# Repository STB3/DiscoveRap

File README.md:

# DiscoveRap
RpRap Electronics Expansion Board for the STM32F429 Discovery Board<p>
Max. 3 Extruders, X, Y, Z Axis<br>
Heated Bed<br>
Case Fan & Light<br>
Fans for each Extruder<br>
TMC260 Stepper driver<br>
USB-OTG, USB-Virtual COM, SD-Card Storage<br>
WLAN option<br>
Needs the STM32F429 Demoboard for operation<br>

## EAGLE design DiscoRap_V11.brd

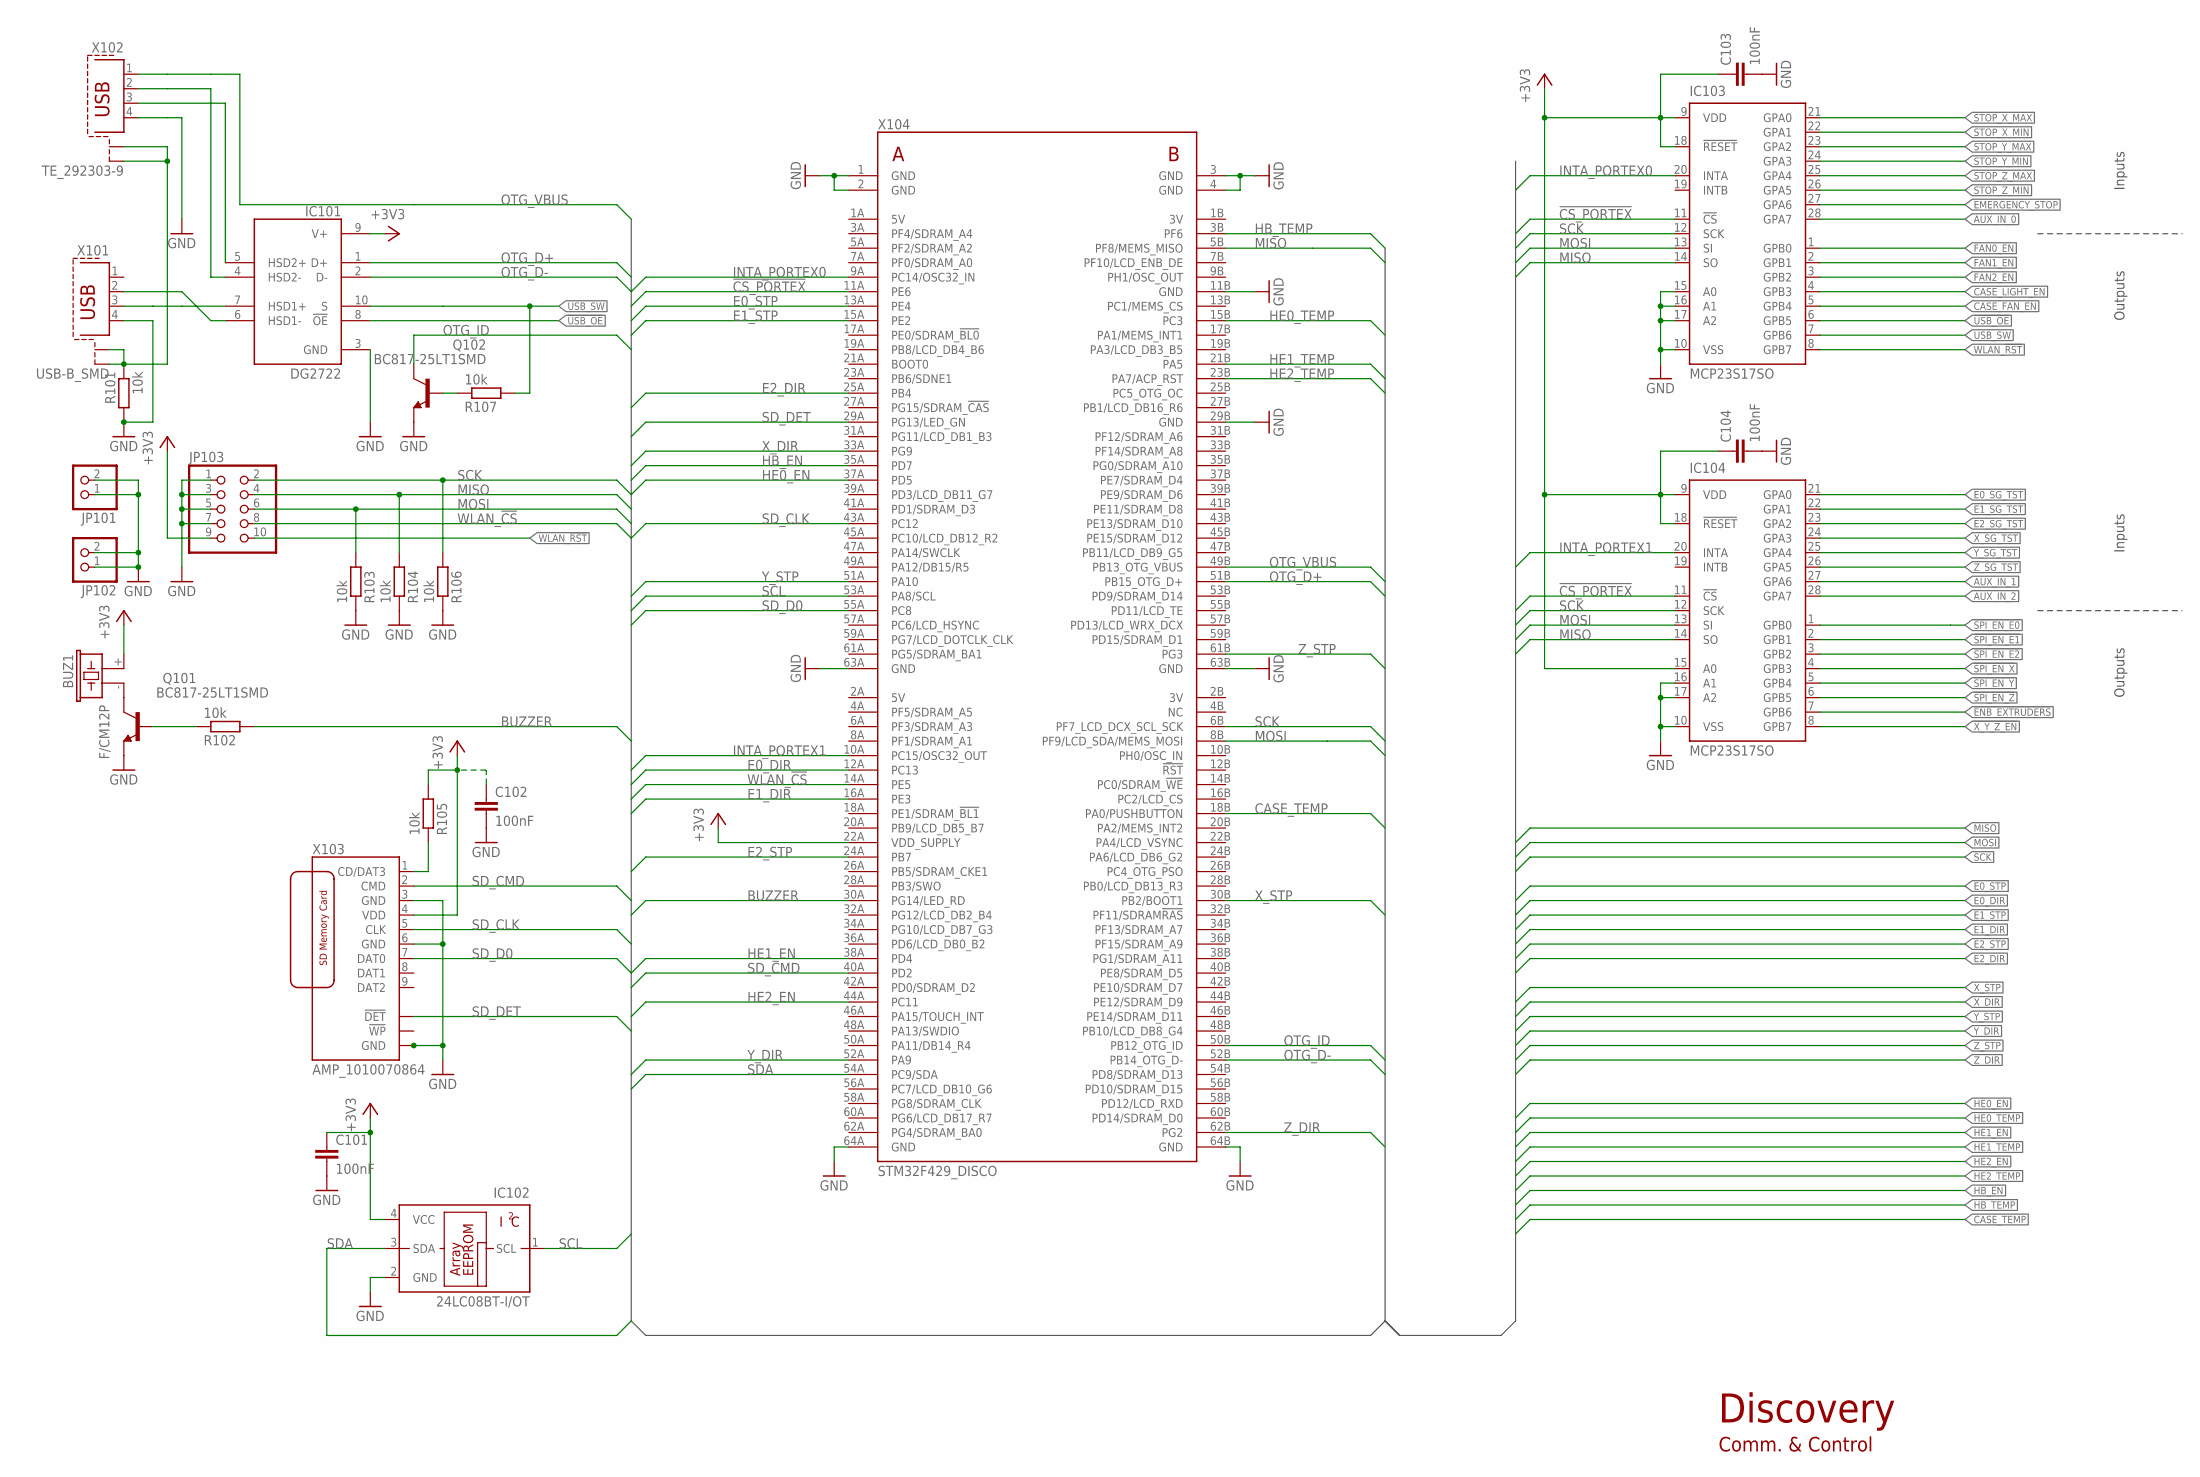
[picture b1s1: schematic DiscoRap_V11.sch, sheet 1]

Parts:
BUZ1: F/CM12P
C101, C102, C103, C104: 100nF; 0805
IC101: DG2722; MINI_QFN_10L
IC102: 24LC08BT-I/OT; SOT23-5L
IC103, IC104: MCP23S17SO; SO28W
JP101, JP102: PINHD-1X2; 1X02
JP103: PINHD-2X5; 2X05
Q101, Q102: BC817-25LT1SMD; SOT23-BEC
R101, R102, R103, R104, R105, R106, R107: 10k; 0805
X101: USB-B_SMD; USB_B_SMD
X102: TE_292303-9; TE_USB_A_SMD
X103: AMP_1010070864
X104: STM32F429_DISCO; STM429_DISCOVERY

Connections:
!CS_PORTEX: IC103.11 (!CS), IC104.11 (!CS), X104.11A (PE6)
!ENB_EXTRUDERS: IC104.7 (GPB6); also elsewhere on the board
!SPI_EN_E0: IC104.1 (GPB0); also elsewhere on the board
!SPI_EN_E1: IC104.2 (GPB1); also elsewhere on the board
!SPI_EN_E2: IC104.3 (GPB2); also elsewhere on the board
!SPI_EN_X: IC104.4 (GPB3); also elsewhere on the board
!SPI_EN_Y: IC104.5 (GPB4); also elsewhere on the board
!SPI_EN_Z: IC104.6 (GPB5); also elsewhere on the board
!USB_OE: IC101.8 (!OE), IC103.6 (GPB5)
!X_Y_Z_EN: IC104.8 (GPB7); also elsewhere on the board
+3V3: BUZ1.+ (1), C101.1, C102.1, C103.1, C104.1, IC101.9 (V+), IC102.4 (VCC), IC103.9 (VDD), IC103.18 (!RESET), IC104.9 (VDD), IC104.15 (A0), IC104.18 (!RESET), JP103.9, R105.2, X103.4 (VDD), X104.22A (VDD_SUPPLY); also elsewhere on the board
AUX_IN_0: IC103.28 (GPA7); also elsewhere on the board
AUX_IN_1: IC104.27 (GPA6); also elsewhere on the board
AUX_IN_2: IC104.28 (GPA7); also elsewhere on the board
BUZZER: R102.2, X104.30A (PG14/LED_RD)
CASE_FAN_EN: IC103.5 (GPB4); also elsewhere on the board
CASE_LIGHT_EN: IC103.4 (GPB3); also elsewhere on the board
CASE_TEMP: X104.18B (PA0/PUSHBUTTON); also elsewhere on the board
E0_DIR: X104.12A (PC13); also elsewhere on the board
E0_SG_TST: IC104.21 (GPA0); also elsewhere on the board
E0_STP: X104.13A (PE4); also elsewhere on the board
E1_DIR: X104.16A (PE3); also elsewhere on the board
E1_SG_TST: IC104.22 (GPA1); also elsewhere on the board
E1_STP: X104.15A (PE2); also elsewhere on the board
E2_DIR: X104.25A (PB4); also elsewhere on the board
E2_SG_TST: IC104.23 (GPA2); also elsewhere on the board
E2_STP: X104.24A (PB7); also elsewhere on the board
EMERGENCY_STOP: IC103.27 (GPA6); also elsewhere on the board
FAN0_EN: IC103.1 (GPB0); also elsewhere on the board
FAN1_EN: IC103.2 (GPB1); also elsewhere on the board
FAN2_EN: IC103.3 (GPB2); also elsewhere on the board
GND: C101.2, C102.2, C103.2, C104.2, IC101.3 (GND), IC102.2 (GND), IC103.10 (VSS), IC103.15 (A0), IC103.16 (A1), IC103.17 (A2), IC104.10 (VSS), IC104.16 (A1), IC104.17 (A2), JP101.1, JP101.2, JP102.1, JP102.2, JP103.1, JP103.3, JP103.5, JP103.7, Q101.E, Q102.E, R101.2, R103.1, R104.1, R106.1, X101.4, X102.4, X103.3 (GND), X103.6 (GND), X103.GND1 (GND), X103.GND2 (GND), X103.GND3 (GND), X103.GND4 (GND), X104.1 (GND), X104.2 (GND), X104.3 (GND), X104.4 (GND), X104.11B (GND), X104.29B (GND), X104.63A (GND), X104.63B (GND), X104.64A (GND), X104.64B (GND); also elsewhere on the board
HB_EN: X104.35A (PD7); also elsewhere on the board
HB_TEMP: X104.3B (PF6); also elsewhere on the board
HE0_EN: X104.37A (PD5); also elsewhere on the board
HE0_TEMP: X104.15B (PC3); also elsewhere on the board
HE1_EN: X104.38A (PD4); also elsewhere on the board
HE1_TEMP: X104.21B (PA5); also elsewhere on the board
HE2_EN: X104.44A (PC11); also elsewhere on the board
HE2_TEMP: X104.23B (PA7/ACP_RST); also elsewhere on the board
INTA_PORTEX0: IC103.20 (INTA), X104.9A (PC14/OSC32_IN)
INTA_PORTEX1: IC104.20 (INTA), X104.10A (PC15/OSC32_OUT)
MISO: IC103.14 (SO), IC104.14 (SO), JP103.4, R104.2, X104.5B (PF8/MEMS_MISO); also elsewhere on the board
MOSI: IC103.13 (SI), IC104.13 (SI), JP103.6, R103.2, X104.8B (PF9/LCD_SDA/MEMS_MOSI); also elsewhere on the board
unnamed: R105.1, X103.1 (CD/DAT3)
unnamed: IC101.4 (HSD2-), X102.2
unnamed: IC101.5 (HSD2+), X102.3
unnamed: IC101.7 (HSD1+), X101.3
unnamed: BUZ1.- (2), Q101.C
unnamed: IC101.6 (HSD1-), X101.2
unnamed: R101.1, X101.5 (S1), X101.6 (S2), X102.5 (S1), X102.6 (S2)
unnamed: Q102.B, R107.1
unnamed: Q101.B, R102.1
OTG_D+: IC101.1 (D+), X104.51B (PB15_OTG_D+)
OTG_D-: IC101.2 (D-), X104.52B (PB14_OTG_D-)
OTG_ID: Q102.C, X104.50B (PB12_OTG_ID)
OTG_VBUS: X102.1, X104.49B (PB13_OTG_VBUS)
SCK: IC103.12 (SCK), IC104.12 (SCK), JP103.2, R106.2, X104.6B (PF7_LCD_DCX_SCL_SCK); also elsewhere on the board
SCL: IC102.1 (SCL), X104.53A (PA8/SCL)
SDA: IC102.3 (SDA), X104.54A (PC9/SDA)
SD_CLK: X103.5 (CLK), X104.43A (PC12)
SD_CMD: X103.2 (CMD), X104.40A (PD2)
SD_D0: X103.7 (DAT0), X104.55A (PC8)
SD_DET: X103.DET (!DET), X104.29A (PG13/LED_GN)
STOP_X_MAX: IC103.21 (GPA0); also elsewhere on the board
STOP_X_MIN: IC103.22 (GPA1); also elsewhere on the board
STOP_Y_MAX: IC103.23 (GPA2); also elsewhere on the board
STOP_Y_MIN: IC103.24 (GPA3); also elsewhere on the board
STOP_Z_MAX: IC103.25 (GPA4); also elsewhere on the board
STOP_Z_MIN: IC103.26 (GPA5); also elsewhere on the board
USB_SW: IC101.10 (S), IC103.7 (GPB6), R107.2
WLAN_!CS: JP103.8, X104.14A (PE5)
WLAN_!RST: IC103.8 (GPB7), JP103.10
X_DIR: X104.33A (PG9); also elsewhere on the board
X_SG_TST: IC104.24 (GPA3); also elsewhere on the board
X_STP: X104.30B (PB2/BOOT1); also elsewhere on the board
Y_DIR: X104.52A (PA9); also elsewhere on the board
Y_SG_TST: IC104.25 (GPA4); also elsewhere on the board
Y_STP: X104.51A (PA10); also elsewhere on the board
Z_DIR: X104.62B (PG2); also elsewhere on the board
Z_SG_TST: IC104.26 (GPA5); also elsewhere on the board
Z_STP: X104.61B (PG3); also elsewhere on the board

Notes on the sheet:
Inputs
Outputs
Discovery
Comm. & Control

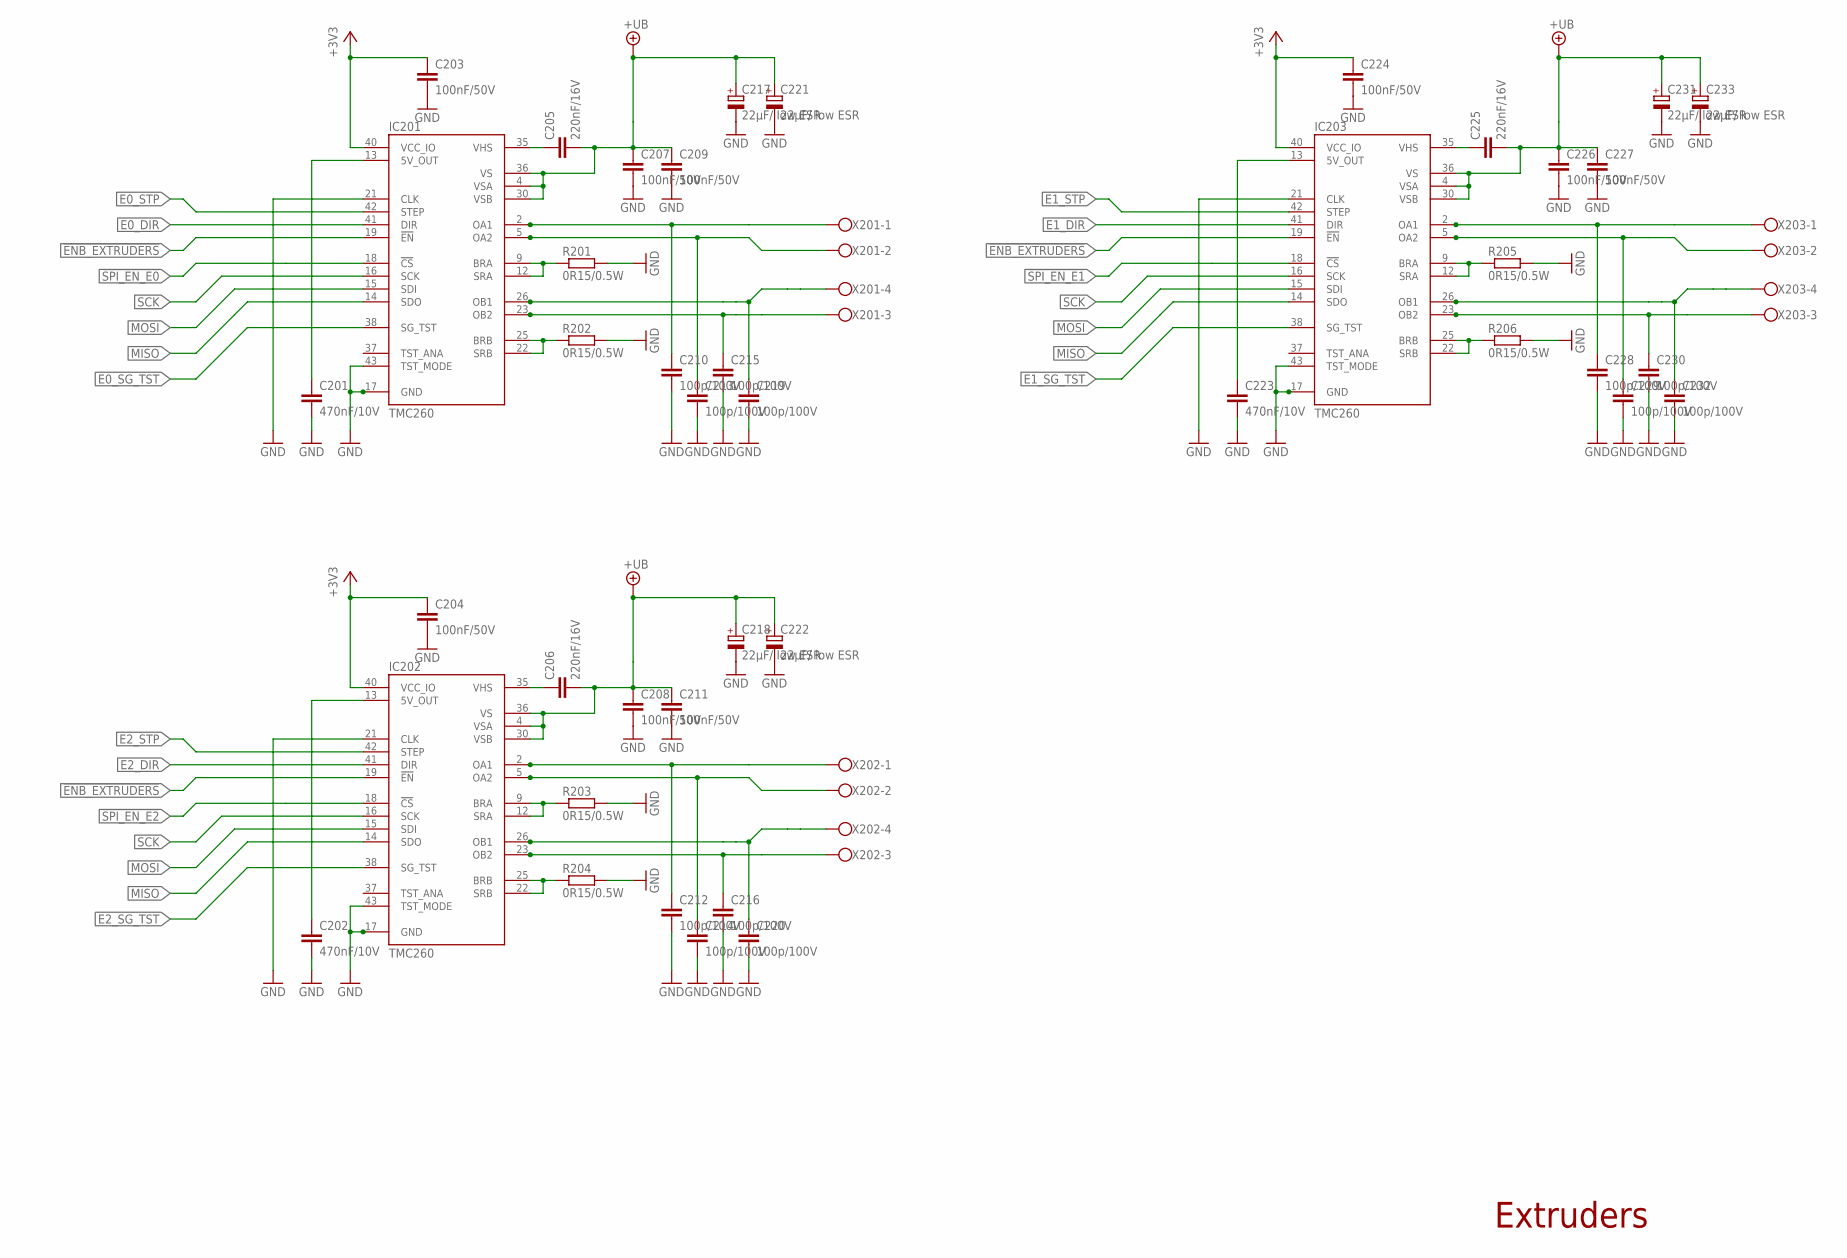
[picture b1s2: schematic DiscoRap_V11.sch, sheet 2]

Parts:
C201, C202, C223: 470nF/10V; 0805
C203, C204, C207, C208, C209, C211, C224, C226, C227: 100nF/50V; 0805
C205, C206, C225: 220nF/16V; 0805
C210, C212, C213, C214, C215, C216, C219, C220, C228, C229, C230, C232: 100p/100V; 0805
C217, C218, C221, C222, C231, C233: 22µF/ low ESR; SANYO-OSCON_SMD_B6
IC201, IC202, IC203: TMC260; SQFP-S-10X10-44
R201, R202, R203, R204, R205, R206: 0R15/0.5W; R1206
X201, X202, X203: W237-4

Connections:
!ENB_EXTRUDERS: IC201.19 (!EN), IC202.19 (!EN), IC203.19 (!EN); also elsewhere on the board
!SPI_EN_E0: IC201.18 (!CS); also elsewhere on the board
!SPI_EN_E1: IC203.18 (!CS); also elsewhere on the board
!SPI_EN_E2: IC202.18 (!CS); also elsewhere on the board
+3V3: C203.1, C204.1, C224.1, IC201.40 (VCC_IO), IC202.40 (VCC_IO), IC203.40 (VCC_IO); also elsewhere on the board
+UB: C205.2, C206.2, C207.1, C208.1, C209.1, C211.1, C217.+, C218.+, C221.+, C222.+, C225.2, C226.1, C227.1, C231.+, C233.+, IC201.4 (VSA), IC201.30 (VSB), IC201.36 (VS), IC202.4 (VSA), IC202.30 (VSB), IC202.36 (VS), IC203.4 (VSA), IC203.30 (VSB), IC203.36 (VS); also elsewhere on the board
E0_A1: C210.1, IC201.2 (OA1), IC201.3 (OA1), IC201.7 (OA1), IC201.8 (OA1), X201.1
E0_A2: C213.1, IC201.5 (OA2), IC201.6 (OA2), IC201.10 (OA2), IC201.11 (OA2), X201.2
E0_A3: C229.1, IC203.5 (OA2), IC203.6 (OA2), IC203.10 (OA2), IC203.11 (OA2), X203.2
E0_A4: C228.1, IC203.2 (OA1), IC203.3 (OA1), IC203.7 (OA1), IC203.8 (OA1), X203.1
E0_A5: C214.1, IC202.5 (OA2), IC202.6 (OA2), IC202.10 (OA2), IC202.11 (OA2), X202.2
E0_A6: C212.1, IC202.2 (OA1), IC202.3 (OA1), IC202.7 (OA1), IC202.8 (OA1), X202.1
E0_B1: C219.1, IC201.26 (OB1), IC201.27 (OB1), IC201.31 (OB1), IC201.32 (OB1), X201.4
E0_B2: C215.1, IC201.23 (OB2), IC201.24 (OB2), IC201.28 (OB2), IC201.29 (OB2), X201.3
E0_B3: C232.1, IC203.26 (OB1), IC203.27 (OB1), IC203.31 (OB1), IC203.32 (OB1), X203.4
E0_B4: C230.1, IC203.23 (OB2), IC203.24 (OB2), IC203.28 (OB2), IC203.29 (OB2), X203.3
E0_B5: C220.1, IC202.26 (OB1), IC202.27 (OB1), IC202.31 (OB1), IC202.32 (OB1), X202.4
E0_B6: C216.1, IC202.23 (OB2), IC202.24 (OB2), IC202.28 (OB2), IC202.29 (OB2), X202.3
E0_DIR: IC201.41 (DIR); also elsewhere on the board
E0_SG_TST: IC201.38 (SG_TST); also elsewhere on the board
E0_STP: IC201.42 (STEP); also elsewhere on the board
E1_DIR: IC203.41 (DIR); also elsewhere on the board
E1_SG_TST: IC203.38 (SG_TST); also elsewhere on the board
E1_STP: IC203.42 (STEP); also elsewhere on the board
E2_DIR: IC202.41 (DIR); also elsewhere on the board
E2_SG_TST: IC202.38 (SG_TST); also elsewhere on the board
E2_STP: IC202.42 (STEP); also elsewhere on the board
GND: C201.2, C202.2, C203.2, C204.2, C207.2, C208.2, C209.2, C210.2, C211.2, C212.2, C213.2, C214.2, C215.2, C216.2, C217.-, C218.-, C219.2, C220.2, C221.-, C222.-, C223.2, C224.2, C226.2, C227.2, C228.2, C229.2, C230.2, C231.-, C232.2, C233.-, IC201.17 (GND), IC201.21 (CLK), IC201.39 (GND), IC201.43 (TST_MODE), IC201.44 (GND), IC202.17 (GND), IC202.21 (CLK), IC202.39 (GND), IC202.43 (TST_MODE), IC202.44 (GND), IC203.17 (GND), IC203.21 (CLK), IC203.39 (GND), IC203.43 (TST_MODE), IC203.44 (GND), R201.2, R202.2, R203.2, R204.2, R205.2, R206.2; also elsewhere on the board
MISO: IC201.14 (SDO), IC202.14 (SDO), IC203.14 (SDO); also elsewhere on the board
MOSI: IC201.15 (SDI), IC202.15 (SDI), IC203.15 (SDI); also elsewhere on the board
unnamed: C205.1, IC201.35 (VHS)
unnamed: IC201.9 (BRA), IC201.12 (SRA), R201.1
unnamed: IC201.22 (SRB), IC201.25 (BRB), R202.1
unnamed: C201.1, IC201.13 (5V_OUT)
unnamed: C225.1, IC203.35 (VHS)
unnamed: IC203.9 (BRA), IC203.12 (SRA), R205.1
unnamed: IC203.22 (SRB), IC203.25 (BRB), R206.1
unnamed: C223.1, IC203.13 (5V_OUT)
unnamed: C206.1, IC202.35 (VHS)
unnamed: IC202.9 (BRA), IC202.12 (SRA), R203.1
unnamed: IC202.22 (SRB), IC202.25 (BRB), R204.1
unnamed: C202.1, IC202.13 (5V_OUT)
SCK: IC201.16 (SCK), IC202.16 (SCK), IC203.16 (SCK); also elsewhere on the board

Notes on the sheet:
Extruders

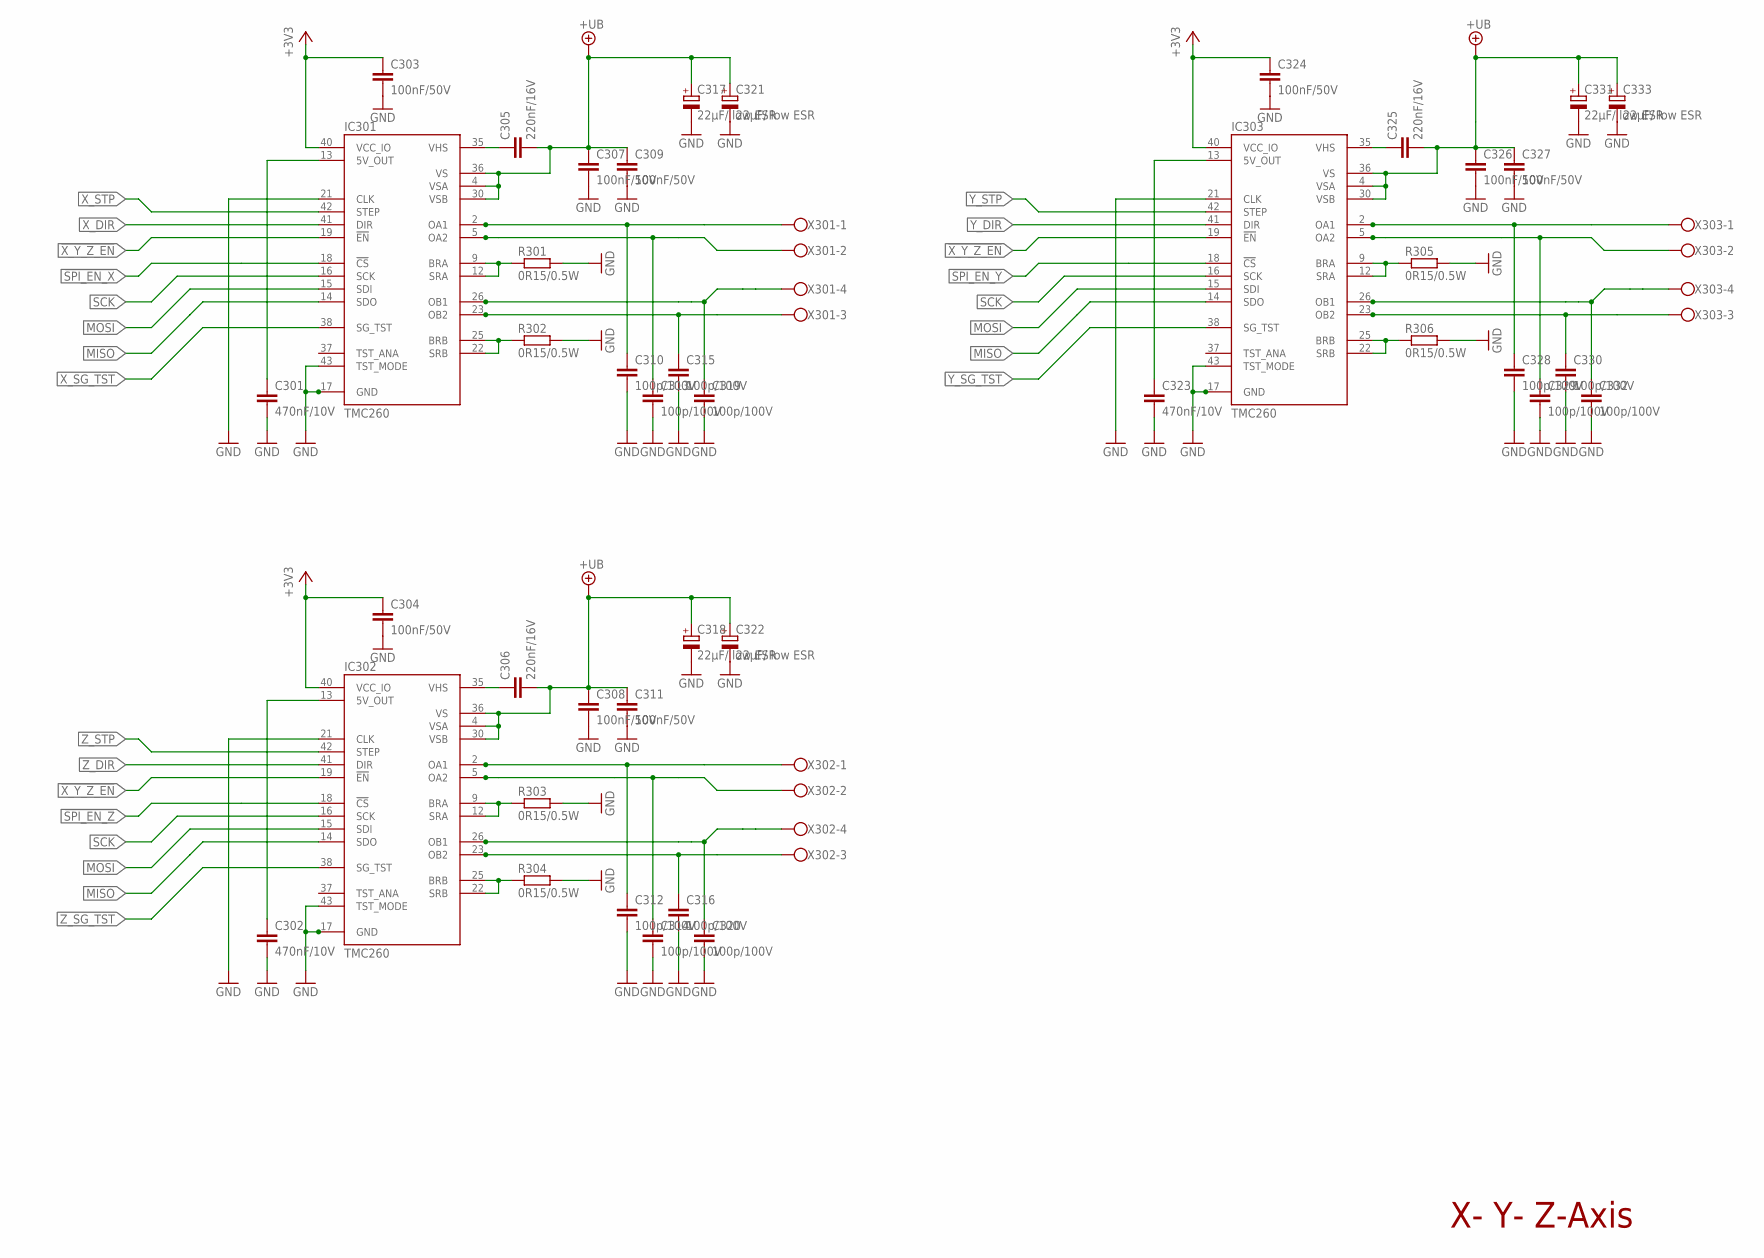
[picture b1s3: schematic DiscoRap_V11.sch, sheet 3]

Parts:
C301, C302, C323: 470nF/10V; 0805
C303, C304, C307, C308, C309, C311, C324, C326, C327: 100nF/50V; 0805
C305, C306, C325: 220nF/16V; 0805
C310, C312, C313, C314, C315, C316, C319, C320, C328, C329, C330, C332: 100p/100V; 0805
C317, C318, C321, C322, C331, C333: 22µF/ low ESR; SANYO-OSCON_SMD_B6
IC301, IC302, IC303: TMC260; SQFP-S-10X10-44
R301, R302, R303, R304, R305, R306: 0R15/0.5W; R1206
X301, X302, X303: W237-4

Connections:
!SPI_EN_X: IC301.18 (!CS); also elsewhere on the board
!SPI_EN_Y: IC303.18 (!CS); also elsewhere on the board
!SPI_EN_Z: IC302.18 (!CS); also elsewhere on the board
!X_Y_Z_EN: IC301.19 (!EN), IC302.19 (!EN), IC303.19 (!EN); also elsewhere on the board
+3V3: C303.1, C304.1, C324.1, IC301.40 (VCC_IO), IC302.40 (VCC_IO), IC303.40 (VCC_IO); also elsewhere on the board
+UB: C305.2, C306.2, C307.1, C308.1, C309.1, C311.1, C317.+, C318.+, C321.+, C322.+, C325.2, C326.1, C327.1, C331.+, C333.+, IC301.4 (VSA), IC301.30 (VSB), IC301.36 (VS), IC302.4 (VSA), IC302.30 (VSB), IC302.36 (VS), IC303.4 (VSA), IC303.30 (VSB), IC303.36 (VS); also elsewhere on the board
E0_A7: C313.1, IC301.5 (OA2), IC301.6 (OA2), IC301.10 (OA2), IC301.11 (OA2), X301.2
E0_A8: C310.1, IC301.2 (OA1), IC301.3 (OA1), IC301.7 (OA1), IC301.8 (OA1), X301.1
E0_A9: C329.1, IC303.5 (OA2), IC303.6 (OA2), IC303.10 (OA2), IC303.11 (OA2), X303.2
E0_A10: C328.1, IC303.2 (OA1), IC303.3 (OA1), IC303.7 (OA1), IC303.8 (OA1), X303.1
E0_A11: C314.1, IC302.5 (OA2), IC302.6 (OA2), IC302.10 (OA2), IC302.11 (OA2), X302.2
E0_A12: C312.1, IC302.2 (OA1), IC302.3 (OA1), IC302.7 (OA1), IC302.8 (OA1), X302.1
E0_B7: C319.1, IC301.26 (OB1), IC301.27 (OB1), IC301.31 (OB1), IC301.32 (OB1), X301.4
E0_B8: C315.1, IC301.23 (OB2), IC301.24 (OB2), IC301.28 (OB2), IC301.29 (OB2), X301.3
E0_B9: C332.1, IC303.26 (OB1), IC303.27 (OB1), IC303.31 (OB1), IC303.32 (OB1), X303.4
E0_B10: C330.1, IC303.23 (OB2), IC303.24 (OB2), IC303.28 (OB2), IC303.29 (OB2), X303.3
E0_B11: C320.1, IC302.26 (OB1), IC302.27 (OB1), IC302.31 (OB1), IC302.32 (OB1), X302.4
E0_B12: C316.1, IC302.23 (OB2), IC302.24 (OB2), IC302.28 (OB2), IC302.29 (OB2), X302.3
GND: C301.2, C302.2, C303.2, C304.2, C307.2, C308.2, C309.2, C310.2, C311.2, C312.2, C313.2, C314.2, C315.2, C316.2, C317.-, C318.-, C319.2, C320.2, C321.-, C322.-, C323.2, C324.2, C326.2, C327.2, C328.2, C329.2, C330.2, C331.-, C332.2, C333.-, IC301.17 (GND), IC301.21 (CLK), IC301.39 (GND), IC301.43 (TST_MODE), IC301.44 (GND), IC302.17 (GND), IC302.21 (CLK), IC302.39 (GND), IC302.43 (TST_MODE), IC302.44 (GND), IC303.17 (GND), IC303.21 (CLK), IC303.39 (GND), IC303.43 (TST_MODE), IC303.44 (GND), R301.2, R302.2, R303.2, R304.2, R305.2, R306.2; also elsewhere on the board
MISO: IC301.14 (SDO), IC302.14 (SDO), IC303.14 (SDO); also elsewhere on the board
MOSI: IC301.15 (SDI), IC302.15 (SDI), IC303.15 (SDI); also elsewhere on the board
unnamed: C305.1, IC301.35 (VHS)
unnamed: IC301.9 (BRA), IC301.12 (SRA), R301.1
unnamed: IC301.22 (SRB), IC301.25 (BRB), R302.1
unnamed: C301.1, IC301.13 (5V_OUT)
unnamed: C325.1, IC303.35 (VHS)
unnamed: IC303.9 (BRA), IC303.12 (SRA), R305.1
unnamed: IC303.22 (SRB), IC303.25 (BRB), R306.1
unnamed: C323.1, IC303.13 (5V_OUT)
unnamed: C306.1, IC302.35 (VHS)
unnamed: IC302.9 (BRA), IC302.12 (SRA), R303.1
unnamed: IC302.22 (SRB), IC302.25 (BRB), R304.1
unnamed: C302.1, IC302.13 (5V_OUT)
SCK: IC301.16 (SCK), IC302.16 (SCK), IC303.16 (SCK); also elsewhere on the board
X_DIR: IC301.41 (DIR); also elsewhere on the board
X_SG_TST: IC301.38 (SG_TST); also elsewhere on the board
X_STP: IC301.42 (STEP); also elsewhere on the board
Y_DIR: IC303.41 (DIR); also elsewhere on the board
Y_SG_TST: IC303.38 (SG_TST); also elsewhere on the board
Y_STP: IC303.42 (STEP); also elsewhere on the board
Z_DIR: IC302.41 (DIR); also elsewhere on the board
Z_SG_TST: IC302.38 (SG_TST); also elsewhere on the board
Z_STP: IC302.42 (STEP); also elsewhere on the board

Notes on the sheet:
X- Y- Z-Axis

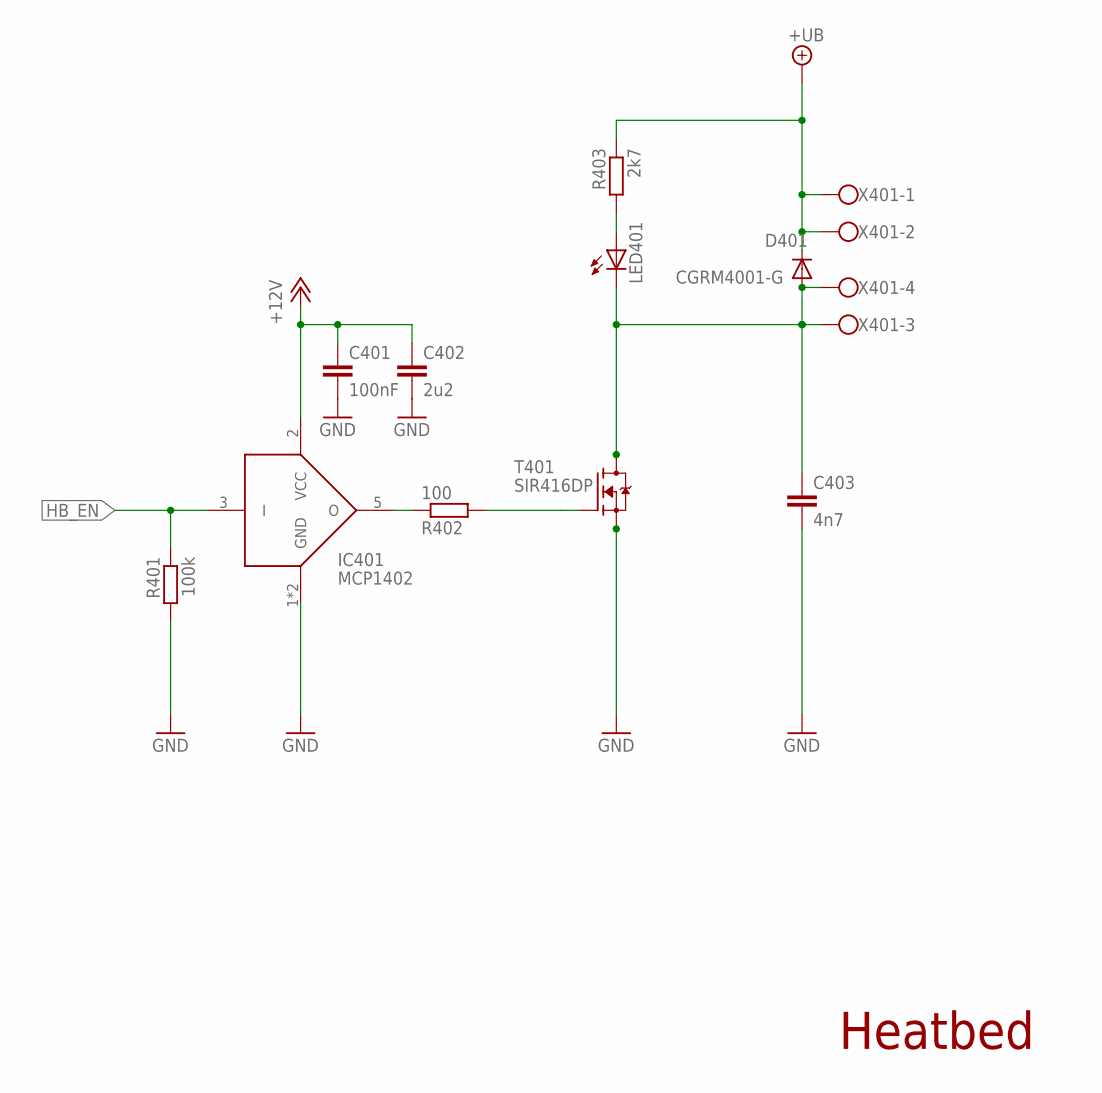
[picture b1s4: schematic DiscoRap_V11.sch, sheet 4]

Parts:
C401: 100nF; 0805
C402: 2u2; 0805
C403: 4n7; 0805
D401: CGRM4001-G; SOD-123_MINI-SMA
IC401: MCP1402; SOT23-5L
LED401: LEDCHIPLED_0805; CHIPLED_0805
R401: 100k; 0805
R402: 100; 0805
R403: 2k7; 0805
T401: SIR416DP; SO-8_POWERPACK
X401: W237-4

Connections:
+12V: C401.1, C402.1, IC401.2 (VCC); also elsewhere on the board
+UB: D401.C, R403.1, X401.1, X401.2; also elsewhere on the board
GND: C401.2, C402.2, C403.2, IC401.1 (GND), IC401.4 (GND), R401.2, T401.1 (S), T401.2 (S), T401.3 (S); also elsewhere on the board
HB_EN: IC401.3 (I), R401.1; also elsewhere on the board
unnamed: R402.2, T401.4 (G)
unnamed: IC401.5 (O), R402.1
unnamed: C403.1, D401.A, LED401.C, T401.5 (D), T401.6 (D), T401.7 (D), T401.8 (D), T401.EXP_PAD (D), X401.3, X401.4
unnamed: LED401.A, R403.2

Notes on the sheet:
Heatbed

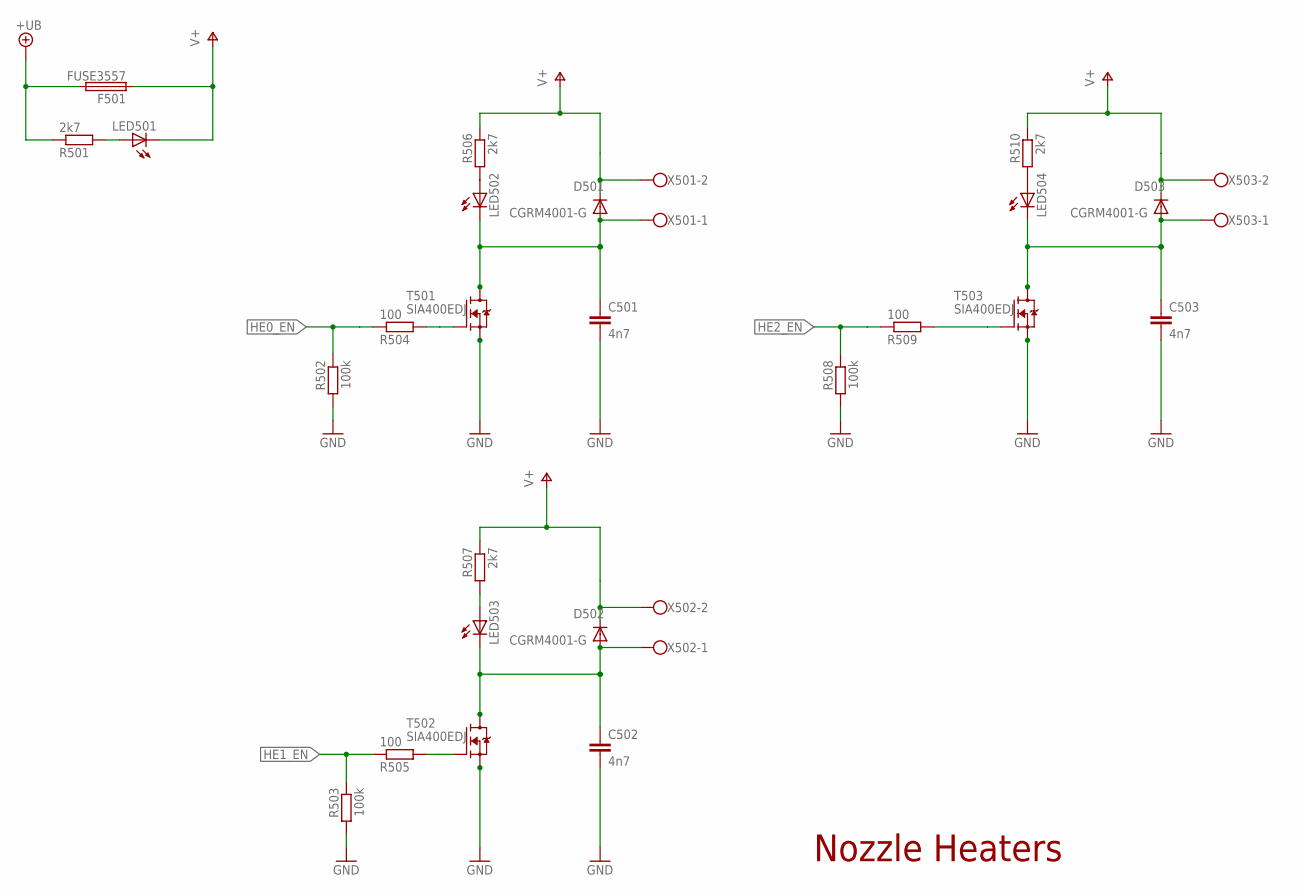
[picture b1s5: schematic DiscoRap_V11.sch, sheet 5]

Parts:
C501, C502, C503: 4n7; 0805
D501, D502, D503: CGRM4001-G; SOD-123_MINI-SMA
F501: FUSE3557; 3557
LED501, LED502, LED503, LED504: LEDCHIPLED_0805; CHIPLED_0805
R501, R506, R507, R510: 2k7; 0805
R502, R503, R508: 100k; 0805
R504, R505, R509: 100; 0805
T501, T502, T503: SIA400EDJ; SC70-6L
X501, X502, X503: W237-102

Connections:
+UB: F501.3 (2), F501.4 (2), R501.1; also elsewhere on the board
GND: C501.2, C502.2, C503.2, R502.2, R503.2, R508.2, T501.4 (S), T501.EXP_SOURCE (S), T502.4 (S), T502.EXP_SOURCE (S), T503.4 (S), T503.EXP_SOURCE (S); also elsewhere on the board
HE0_EN: R502.1, R504.1; also elsewhere on the board
HE1_EN: R503.1, R505.1; also elsewhere on the board
HE2_EN: R508.1, R509.1; also elsewhere on the board
unnamed: R504.2, T501.3 (G)
unnamed: C501.1, D501.A, LED502.C, T501.1 (D), T501.2 (D), T501.5 (D), T501.6 (D), T501.EXP_DRAIN (D), X501.1
unnamed: LED502.A, R506.2
unnamed: R505.2, T502.3 (G)
unnamed: C502.1, D502.A, LED503.C, T502.1 (D), T502.2 (D), T502.5 (D), T502.6 (D), T502.EXP_DRAIN (D), X502.1
unnamed: LED503.A, R507.2
unnamed: R509.2, T503.3 (G)
unnamed: C503.1, D503.A, LED504.C, T503.1 (D), T503.2 (D), T503.5 (D), T503.6 (D), T503.EXP_DRAIN (D), X503.1
unnamed: LED504.A, R510.2
unnamed: LED501.A, R501.2
V+: D501.C, D502.C, D503.C, F501.1, F501.2 (1), LED501.C, R506.1, R507.1, R510.1, X501.2, X502.2, X503.2

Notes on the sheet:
Nozzle Heaters

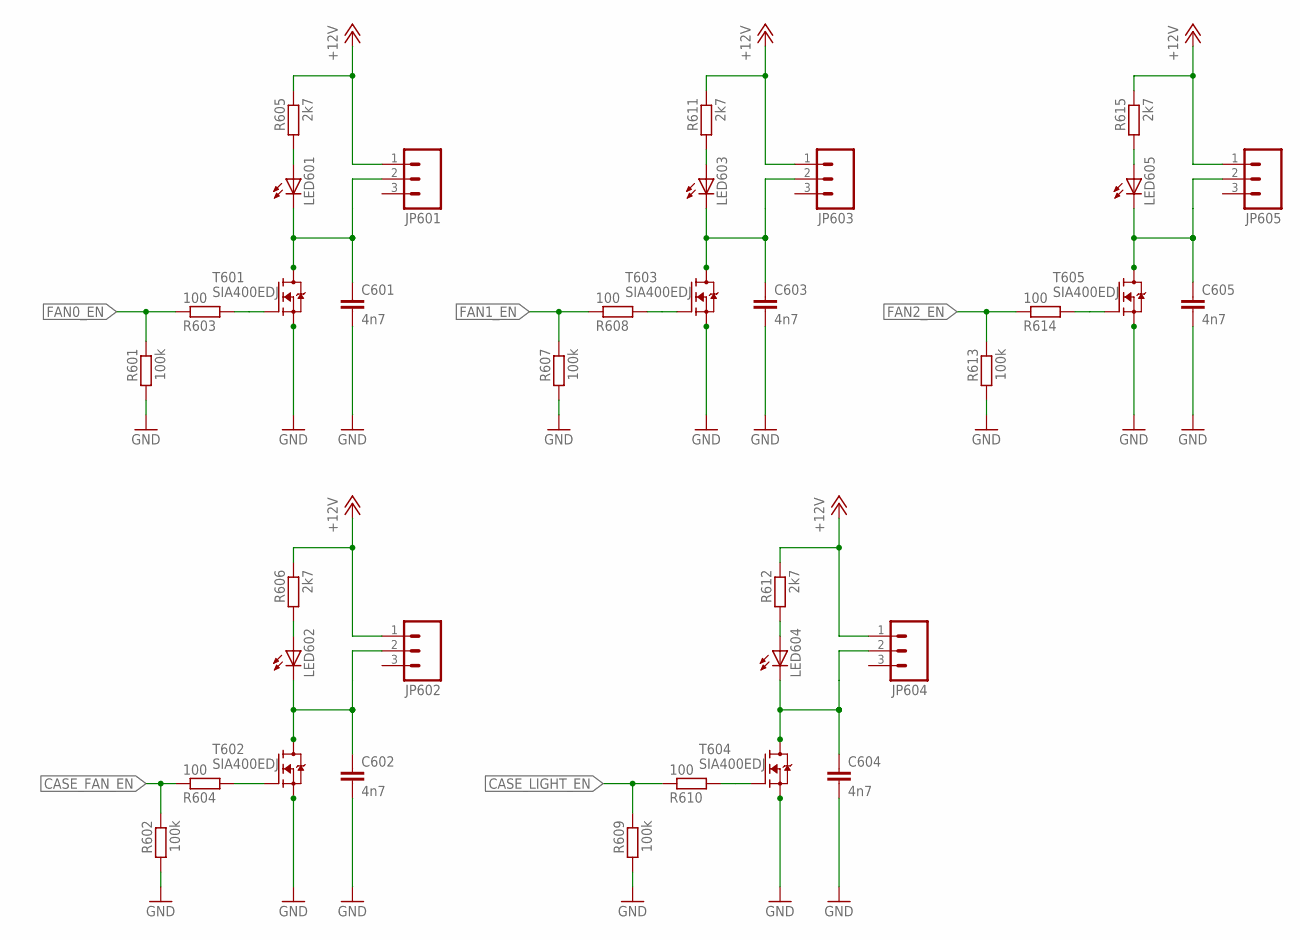
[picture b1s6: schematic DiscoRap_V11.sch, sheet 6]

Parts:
C601, C602, C603, C604, C605: 4n7; 0805
JP601, JP602, JP603, JP604, JP605: M03POLAR; MOLEX-1X3
LED601, LED602, LED603, LED604, LED605: LEDCHIPLED_0805; CHIPLED_0805
R601, R602, R607, R609, R613: 100k; 0805
R603, R604, R608, R610, R614: 100; 0805
R605, R606, R611, R612, R615: 2k7; 0805
T601, T602, T603, T604, T605: SIA400EDJ; SC70-6L

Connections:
+12V: JP601.1, JP602.1, JP603.1, JP604.1, JP605.1, R605.1, R606.1, R611.1, R612.1, R615.1; also elsewhere on the board
CASE_FAN_EN: R602.1, R604.1; also elsewhere on the board
CASE_LIGHT_EN: R609.1, R610.1; also elsewhere on the board
FAN0_EN: R601.1, R603.1; also elsewhere on the board
FAN1_EN: R607.1, R608.1; also elsewhere on the board
FAN2_EN: R613.1, R614.1; also elsewhere on the board
GND: C601.2, C602.2, C603.2, C604.2, C605.2, R601.2, R602.2, R607.2, R609.2, R613.2, T601.4 (S), T601.EXP_SOURCE (S), T602.4 (S), T602.EXP_SOURCE (S), T603.4 (S), T603.EXP_SOURCE (S), T604.4 (S), T604.EXP_SOURCE (S), T605.4 (S), T605.EXP_SOURCE (S); also elsewhere on the board
unnamed: R603.2, T601.3 (G)
unnamed: C601.1, JP601.2, LED601.C, T601.1 (D), T601.2 (D), T601.5 (D), T601.6 (D), T601.EXP_DRAIN (D)
unnamed: LED601.A, R605.2
unnamed: R608.2, T603.3 (G)
unnamed: C603.1, JP603.2, LED603.C, T603.1 (D), T603.2 (D), T603.5 (D), T603.6 (D), T603.EXP_DRAIN (D)
unnamed: LED603.A, R611.2
unnamed: R614.2, T605.3 (G)
unnamed: C605.1, JP605.2, LED605.C, T605.1 (D), T605.2 (D), T605.5 (D), T605.6 (D), T605.EXP_DRAIN (D)
unnamed: LED605.A, R615.2
unnamed: R604.2, T602.3 (G)
unnamed: C602.1, JP602.2, LED602.C, T602.1 (D), T602.2 (D), T602.5 (D), T602.6 (D), T602.EXP_DRAIN (D)
unnamed: LED602.A, R606.2
unnamed: R610.2, T604.3 (G)
unnamed: C604.1, JP604.2, LED604.C, T604.1 (D), T604.2 (D), T604.5 (D), T604.6 (D), T604.EXP_DRAIN (D)
unnamed: LED604.A, R612.2
